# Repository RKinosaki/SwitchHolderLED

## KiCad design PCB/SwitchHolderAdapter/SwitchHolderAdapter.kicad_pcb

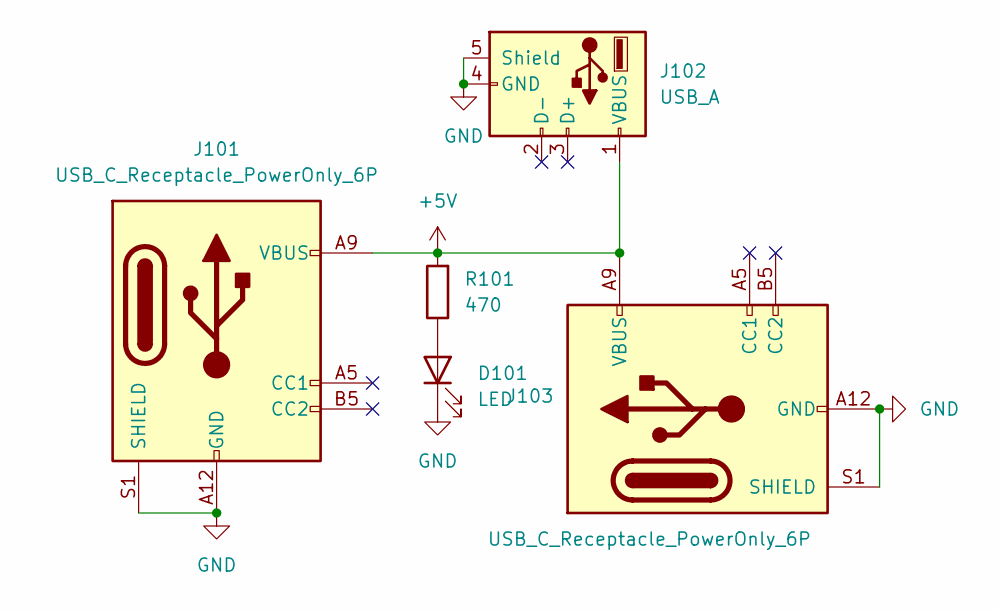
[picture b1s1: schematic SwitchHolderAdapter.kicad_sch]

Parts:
D101: LED; LED_0402_1005Metric
J101, J103: USB_C_Receptacle_PowerOnly_6P; USB_C_Receptacle_GCT_USB4135-GF-A_6P_TopMnt_Horizontal
J102: USB_A; USB_A_Receptacle_GCT_USB1046
R101: 470; R_0402_1005Metric

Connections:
+5V: J101.A9 (VBUS), J101.B9 (VBUS), J102.1 (VBUS), J103.A9 (VBUS), J103.B9 (VBUS), R101.2
GND: D101.1 (K), J101.A12 (GND), J101.B12 (GND), J101.S1 (SHIELD), J102.4 (GND), J102.5 (Shield), J103.A12 (GND), J103.B12 (GND), J103.S1 (SHIELD)
unnamed: D101.2 (A), R101.1

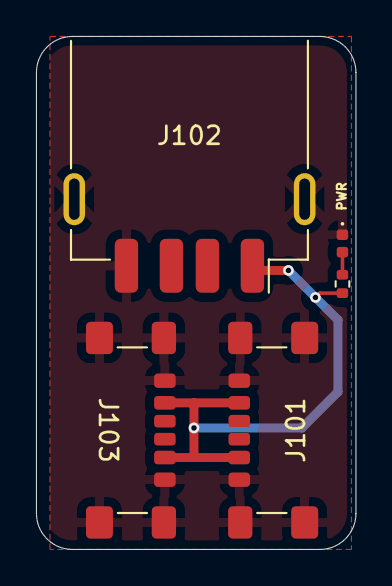
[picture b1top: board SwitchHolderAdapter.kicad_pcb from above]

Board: 2 copper layers, 17.8 x 28.5 mm, 5 parts (0 on the bottom side), 3 nets.

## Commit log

2025-09-05 Switch Holder LED Connector PCB
